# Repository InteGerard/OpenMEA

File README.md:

# OpenMEA
An open source microelectrode array system for closed-loop electrophysiology research

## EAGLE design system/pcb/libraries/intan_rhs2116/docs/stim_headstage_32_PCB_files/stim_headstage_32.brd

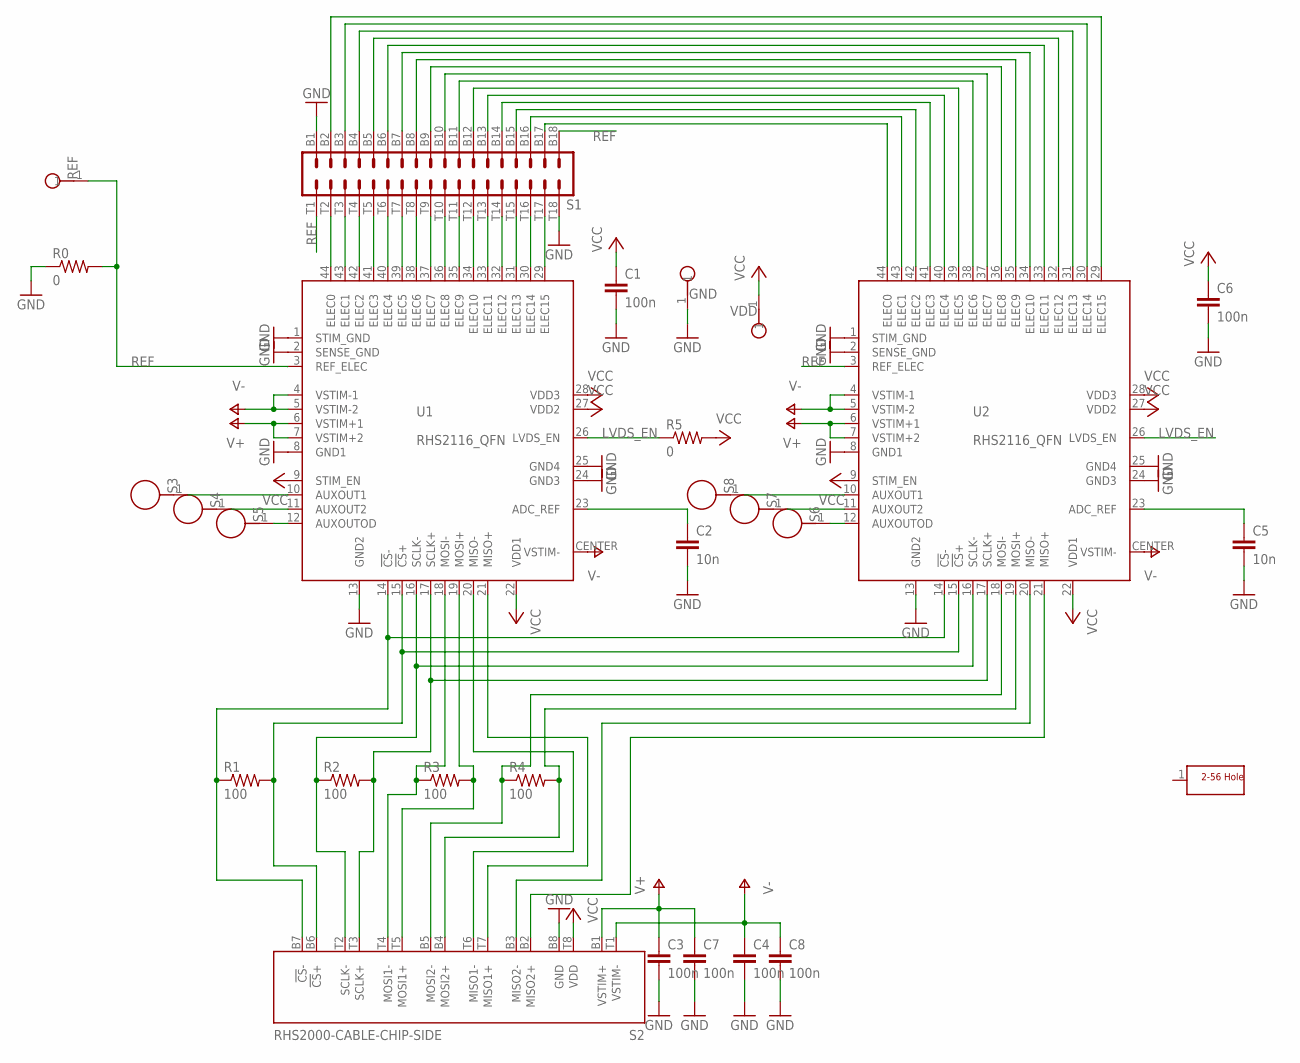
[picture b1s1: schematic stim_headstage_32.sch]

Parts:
C1, C3, C4, C6, C7, C8: 100n; 0402
C2, C5: 10n; 0402
GND: TESTPOINT_SMALL
H1: SCREW_HOLE_2-56
R0: 0; 0402
R1, R2, R3, R4: 100; 0201
R5: 0; 0201
REF: TESTPOINT_SMALL
S1: OMNETICS_A79025
S2: RHS2000-CABLE-CHIP-SIDE; OMNETICS_PZN-16-AA
S3, S4, S5, S6, S7, S8: SMD_CONTACT_1_0_X_1_2; SMD_PAD_1_0_X_1_2
U1, U2: RHS2116_QFN; QFN44_7_X_7
VDD: TESTPOINT_SMALL

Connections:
GND: C1.2, C2.2, C3.2, C4.2, C5.2, C6.2, C7.2, C8.2, GND.1, R0.1, S1.B1, S1.T18, S2.B8 (GND), U1.1 (STIM_GND), U1.2 (SENSE_GND), U1.8 (GND1), U1.13 (GND2), U1.24 (GND3), U1.25 (GND4), U2.1 (STIM_GND), U2.2 (SENSE_GND), U2.8 (GND1), U2.13 (GND2), U2.24 (GND3), U2.25 (GND4)
LVDS_EN: R5.1, U1.26 (LVDS_EN), U2.26 (LVDS_EN)
unnamed: S1.B16, U2.43 (ELEC1)
unnamed: S2.T6 (MISO1-), U1.20 (MISO-)
unnamed: S1.B15, U2.42 (ELEC2)
unnamed: S2.T7 (MISO1+), U1.21 (MISO+)
unnamed: S6.1, U2.12 (AUXOUTOD)
unnamed: S3.1, U1.10 (AUXOUT1)
unnamed: S4.1, U1.11 (AUXOUT2)
unnamed: S5.1, U1.12 (AUXOUTOD)
unnamed: C5.1, U2.23 (ADC_REF)
unnamed: S2.B2 (MISO2+), U2.21 (MISO+)
unnamed: R1.1, S2.B7 (!CS!-), U1.14 (!CS!-), U2.14 (!CS!-)
unnamed: S2.B3 (MISO2-), U2.20 (MISO-)
unnamed: S7.1, U2.11 (AUXOUT2)
unnamed: S8.1, U2.10 (AUXOUT1)
unnamed: S1.T2, U1.44 (ELEC0)
unnamed: S1.T3, U1.43 (ELEC1)
unnamed: S1.T4, U1.42 (ELEC2)
unnamed: S1.T5, U1.41 (ELEC3)
unnamed: S1.T6, U1.40 (ELEC4)
unnamed: S1.T7, U1.39 (ELEC5)
unnamed: S1.T8, U1.38 (ELEC6)
unnamed: S1.T9, U1.37 (ELEC7)
unnamed: S1.T10, U1.36 (ELEC8)
unnamed: S1.T11, U1.35 (ELEC9)
unnamed: S1.T12, U1.34 (ELEC10)
unnamed: S1.T13, U1.33 (ELEC11)
unnamed: S1.T14, U1.32 (ELEC12)
unnamed: S1.T15, U1.31 (ELEC13)
unnamed: S1.T16, U1.30 (ELEC14)
unnamed: S1.T17, U1.29 (ELEC15)
unnamed: S1.B17, U2.44 (ELEC0)
unnamed: S1.B14, U2.41 (ELEC3)
unnamed: S1.B13, U2.40 (ELEC4)
unnamed: S1.B12, U2.39 (ELEC5)
unnamed: R1.2, S2.B6 (!CS!+), U1.15 (!CS!+), U2.15 (!CS!+)
unnamed: R2.1, S2.T2 (SCLK-), U1.16 (SCLK-), U2.16 (SCLK-)
unnamed: R2.2, S2.T3 (SCLK+), U1.17 (SCLK+), U2.17 (SCLK+)
unnamed: R3.1, S2.T4 (MOSI1-), U1.18 (MOSI-)
unnamed: R3.2, S2.T5 (MOSI1+), U1.19 (MOSI+)
unnamed: R4.1, S2.B5 (MOSI2-), U2.18 (MOSI-)
unnamed: R4.2, S2.B4 (MOSI2+), U2.19 (MOSI+)
unnamed: C2.1, U1.23 (ADC_REF)
unnamed: S1.B11, U2.38 (ELEC6)
unnamed: S1.B10, U2.37 (ELEC7)
unnamed: S1.B9, U2.36 (ELEC8)
unnamed: S1.B8, U2.35 (ELEC9)
unnamed: S1.B7, U2.34 (ELEC10)
unnamed: S1.B6, U2.33 (ELEC11)
unnamed: S1.B5, U2.32 (ELEC12)
unnamed: S1.B4, U2.31 (ELEC13)
unnamed: S1.B3, U2.30 (ELEC14)
unnamed: S1.B2, U2.29 (ELEC15)
REF: R0.2, REF.1, S1.B18, S1.T1, U1.3 (REF_ELEC), U2.3 (REF_ELEC)
V+: C3.1, C7.1, S2.B1 (VSTIM+), U1.6 (VSTIM+1), U1.7 (VSTIM+2), U2.6 (VSTIM+1), U2.7 (VSTIM+2)
V-: C4.1, C8.1, S2.T1 (VSTIM-), U1.4 (VSTIM-1), U1.5 (VSTIM-2), U1.CENTER (VSTIM-), U2.4 (VSTIM-1), U2.5 (VSTIM-2), U2.CENTER (VSTIM-)
VCC: C1.1, C6.1, R5.2, S2.T8 (VDD), U1.9 (STIM_EN), U1.22 (VDD1), U1.27 (VDD2), U1.28 (VDD3), U2.9 (STIM_EN), U2.22 (VDD1), U2.27 (VDD2), U2.28 (VDD3), VDD.1

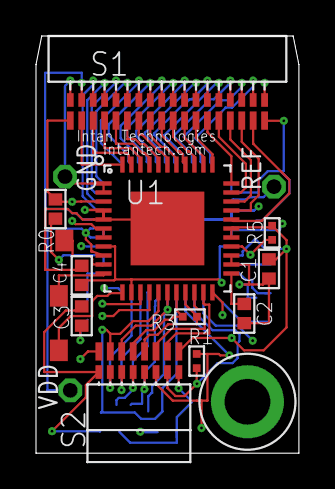
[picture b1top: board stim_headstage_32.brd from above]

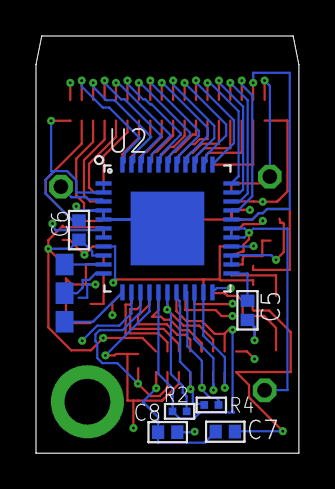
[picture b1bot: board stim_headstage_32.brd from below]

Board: 4 copper layers, 14.6 x 23.2 mm, 28 parts (10 on the bottom side), 58 nets.

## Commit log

2022-06-02 Headstage Check-in
2022-06-02 Added MEAs
2023-02-07 added power board, legacy files
2023-02-25 Added reference designs and lib files
2023-03-01 Add current PCB files
2023-03-03 Power and Intan board checkin
2023-03-06 Added mechanical files
2023-03-06 refactor
2023-03-06 Add updated PCB files
2023-03-06 Update PCB files, move two projects to WIP folder
2023-03-09 Add back Common folder
2023-03-15 Reorganize pcb folder
2023-03-15 Add/update files submitted for PCB orders
2023-03-16 Reorg mechanical
2023-03-16 Adding assembly jig
2023-04-03 Add STEP file of mainboard with holes
2023-05-19 created new LVDS schematic and library
    created new LVDS schematic and library
2023-05-23 update LVDS schematic
2023-05-27 finished headstage modification
2023-05-31 Added references to headstage board
2023-05-31 Finish headstage modification
2023-06-07 finish LVDS board
